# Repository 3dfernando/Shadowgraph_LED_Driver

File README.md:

# Shadowgraph LED Driver
A simple electronic circuit board design for overdriving a pulsed LED flash for shadowgraph purposes. 

*** WARNING: This circuit overdrives an LED with up to 200A of current. COMPONENTS WILL GET BURNED! Be careful in your explorations and make sure you understand the circuit before you start messing with it! ***

# Circuit Description
The circuit schematic, provided in Circuit Diagram.pdf, is very simple. 
24V are provided to a nominally 3.8V LED through a high-power MOSFET (IRF3805) for the duration of the input pulse, which should be very short (order 10us or less) and of very low duty cycle (less than 1% recommended).

The current provided to the LED can reach 200A at full power. 200A will, however, explode the LED bond wires, rendering it useless. Since the LED is very expensive (about $100 as of 2023 for the white LED), it is not recommended to drive at max power. The LED provides a good flash at 100-120A and you should really not exceed 150A (that's where sometimes it may or may not burn depending on other conditions).

There is so much current in such a little time to run the LED that the MOSFET IRF3805 needs a driver IC to provide the inrush current of up to 8A. This obviously cannot be provided by a function generator, which is why the UCC27424 is there to convert the high impedance of the fn. generator to a low impedance required by the MOSFET gate. The UCC27424 can be destroyed if the MOSFET fails. This is because when the MOSFET fails, it can fail such that the Gate and Source terminal are shorted. In this case, the current going through the UCC driver will exceed the 8A rating and burn the IC, so both need to be replaced in this case.

To adjust the amount of current going through the LED, adjust the output voltage of the LM2596 DC-DC converter circuit. This can be done using a small screwdriver to adjust the trimmer-potentiometer in the DC-DC converter. The output voltage will range between 9 and 16V during operation, depending on the amount of current you want for the LED. 

The amount of current running through the LED can be measured with an oscilloscope by watching the voltage drop across the 0.02Ohm resistor. For 100A, for example, we have V=I*R=100A * 0.02Ohm = 2V across the resistor. Since the LED is expensive, you can connect a piece of short wire between the LED terminal connectors (i.e., generate a short circuit), in order to test the system. Once you are confident the current is about 100A or so, connect the LED and test your optics to see if the brightness is sufficient. If it isn't, you can increase the power by using the trimmer-potentiometer in the DC-DC converter, bearing in mind that at about 150A the LED, MOSFET and UCC driver will be destroyed.

Note: The LED has a small thermal mass and will heat up rather quickly if you use a high duty cycle for this driver. The average power dissipation of the LED can exceed 1200W with 1% duty cycle, meaning you will not be able to build a heat sink with acceptable specs for the LED. Best is to simply bolt the LED to a large aluminium block to provide it with thermal mass, and just not run it for too long. The LED may fail over a few minutes if it overheats.

# How to make this
1. First, download Gerbers.zip and send the Gerber files to a PCB manufacturer company.
2. Assemble the PCB according to Circuit Diagram.pdf. Make sure all components are oriented correctly! The bill of materials is provided in BOM.xlsx
3. There is an Operation Instructions.pptx file with directions and pictures on how the PCB looks like. The terminal blocks and DIP8 socket enable replacement of the components that are likely to be damaged if you don't know what you are doing. Make sure you buy extra transistors IRF3805 and UCC27424P chips, as they really can burn very easily until you understand the limitations of this device. 
4. Start testing the board, according to the instructions and warnings in "Circuit Description". Have spare parts - you will need them!

# Known operation conditions
This circuit has been successfully operated at conditions listed below:
* 500Hz, 10us pulse width, indefinitely;
* 500kHz, 0.5us pulse width, for 2-3 seconds (Pulse burst mode in a function generator);
* 10-50kHz, 1us pulse width, for ~30 seconds;
* Minimum pulse width to get any meaningful amount of light is about 100ns (See Pictures/Photodiode measurements folder);
* This circuit is not designed to operate without pulsing (i.e., continuously). Likely all components will fail due to the extremely high currents.

As you can see, this is a very tricky circuit to work with. It provides some real juice for your shadowgraphs, allowing for imaging at very high frame rates. Have fun building it!

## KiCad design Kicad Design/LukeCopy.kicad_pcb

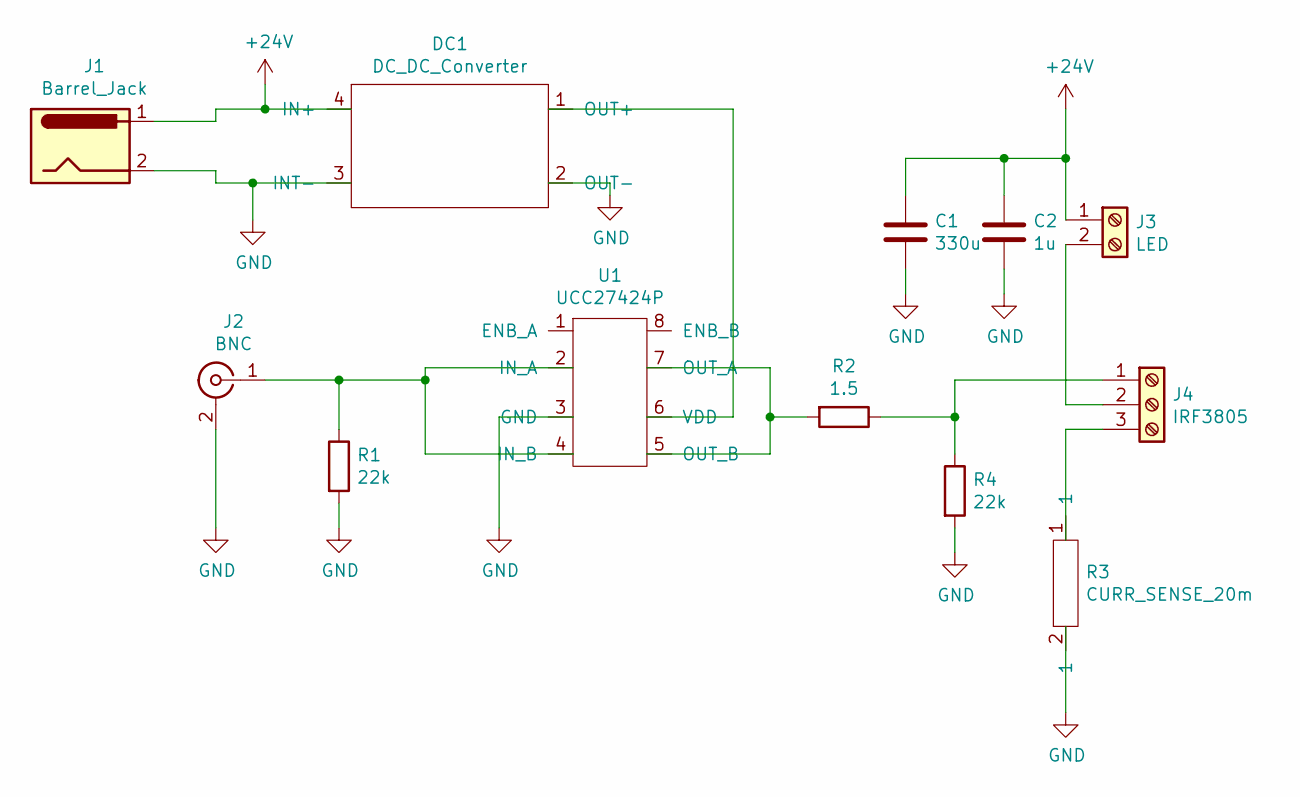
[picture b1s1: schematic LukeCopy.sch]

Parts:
C1: 330u; CP_Radial_D5.0mm_P2.50mm
C2: 1u; C_Disc_D5.1mm_W3.2mm_P5.00mm
DC1: DC_DC_Converter; DCDC_Converter
J1: Barrel_Jack; BarrelJack_Horizontal
J2: BNC; BNC_Connector
J3: LED; TerminalBlock_bornier-2_P5.08mm
J4: IRF3805; TerminalBlock_bornier-3_P5.08mm
R1, R4: 22k; R_Axial_DIN0204_L3.6mm_D1.6mm_P7.62mm_Horizontal
R2: 1.5; R_Axial_DIN0207_L6.3mm_D2.5mm_P10.16mm_Horizontal
R3: CURR_SENSE_20m; CurrentSenseResistor
U1: UCC27424P; DIP-8_W7.62mm

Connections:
+24V: C1.1, C2.1, DC1.4 (IN+), J1.1, J3.1
GND: C1.2, C2.2, DC1.2 (OUT-), DC1.3 (INT-), J1.2, J2.2 (Ext), R1.2, R3.2, R4.2, U1.3 (GND)
unnamed: DC1.1 (OUT+), U1.6 (VDD)
unnamed: J2.1 (In), R1.1, U1.2 (IN_A), U1.4 (IN_B)
unnamed: J3.2, J4.2
unnamed: J4.1, R2.1, R4.1
unnamed: J4.3, R3.1
unnamed: R2.2, U1.5 (OUT_B), U1.7 (OUT_A)

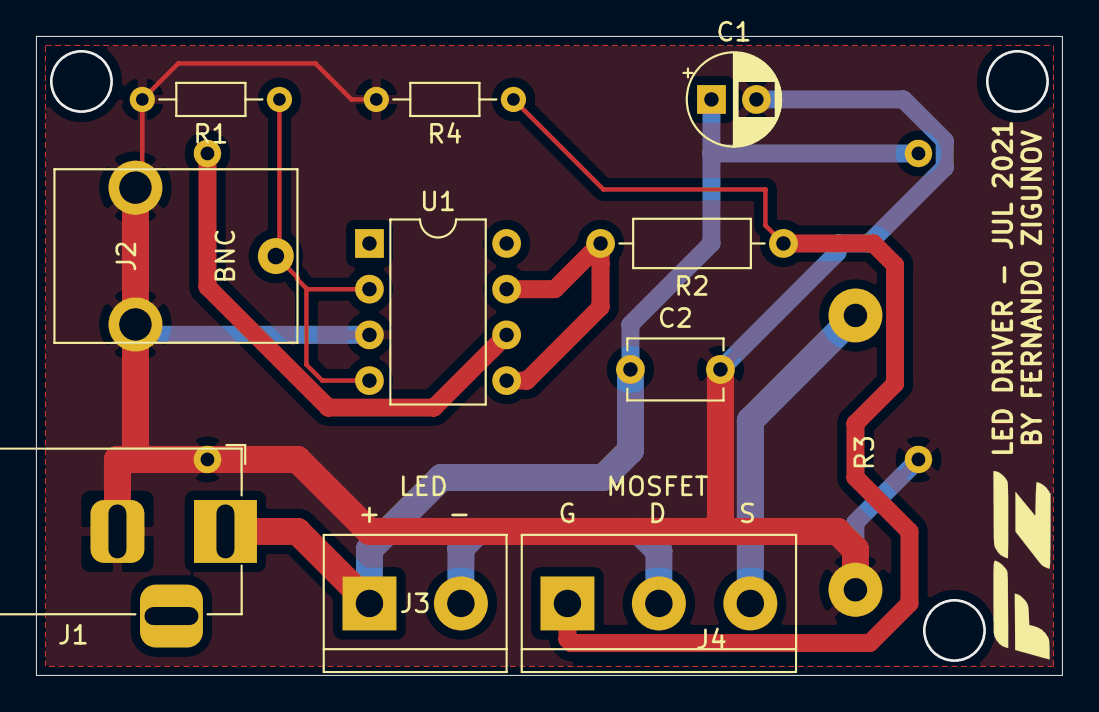
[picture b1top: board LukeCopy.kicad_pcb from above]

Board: 2 copper layers, 57.0 x 35.5 mm, 12 parts (1 on the bottom side), 8 nets.

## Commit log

2023-06-23 Initial upload
